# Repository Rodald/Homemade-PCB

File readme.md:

# Homemade-PCB
The goal for this Project is to manufacture PCBs at home using DIY UV photolithography.
This Repository includes two different PCB designs.

## Benchmarking PCB
The benchmark PCB includes 5 different tests:
* Trace width
* Isolation Clearance
* Light Exposure Time & Bleeding
* Drill Hole tests
* Fonts

## Motion Suit PCB
The goal:

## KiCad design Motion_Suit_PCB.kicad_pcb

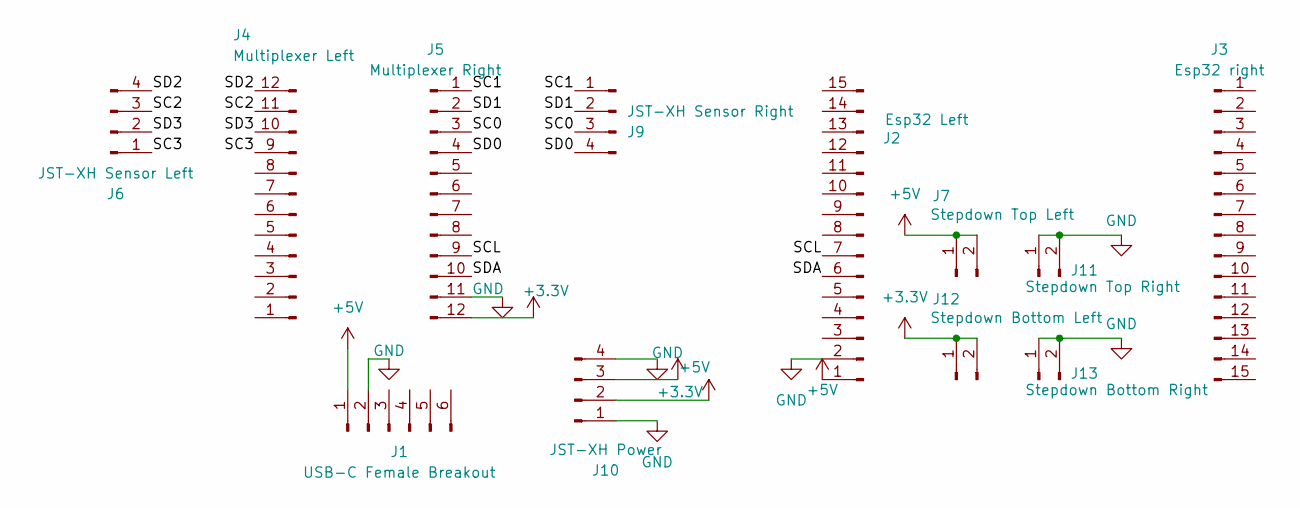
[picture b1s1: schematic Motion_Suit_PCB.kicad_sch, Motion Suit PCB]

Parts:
J1: USB-C Female Breakout; PinHeader_1x06_P2.54mm_Horizontal
J2: Esp32 Left; PinHeader_1x15_P2.54mm_Vertical
J3: Esp32 right; PinHeader_1x15_P2.54mm_Vertical
J4: Multiplexer Left; PinHeader_1x12_P2.54mm_Vertical
J5: Multiplexer Right; PinHeader_1x12_P2.54mm_Vertical
J6: JST-XH Sensor Left; JST_XH_B4B-XH-A_1x04_P2.50mm_Vertical
J7: Stepdown Top Left; PinHeader_1x02_P2.54mm_Horizontal
J9: JST-XH Sensor Right; JST_XH_B4B-XH-A_1x04_P2.50mm_Vertical
J10: JST-XH Power; JST_XH_B4B-XH-A_1x04_P2.50mm_Vertical
J11: Stepdown Top Right; PinHeader_1x02_P2.54mm_Horizontal
J12: Stepdown Bottom Left; PinHeader_1x02_P2.54mm_Horizontal
J13: Stepdown Bottom Right; PinHeader_1x02_P2.54mm_Horizontal

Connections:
+3.3V: J5.12, J10.2, J12.1, J12.2
+5V: J1.1, J2.1, J7.1, J7.2, J10.3
/SC0: J5.3, J9.3
/SC1: J5.1, J9.1
/SC2: J4.11, J6.3
/SC3: J4.9, J6.1
/SCL: J2.7, J5.9
/SD0: J5.4, J9.4
/SD1: J5.2, J9.2
/SD2: J4.12, J6.4
/SD3: J4.10, J6.2
/SDA: J2.6, J5.10
GND: J1.2, J2.2, J5.11, J10.1, J10.4, J11.1, J11.2, J13.1, J13.2

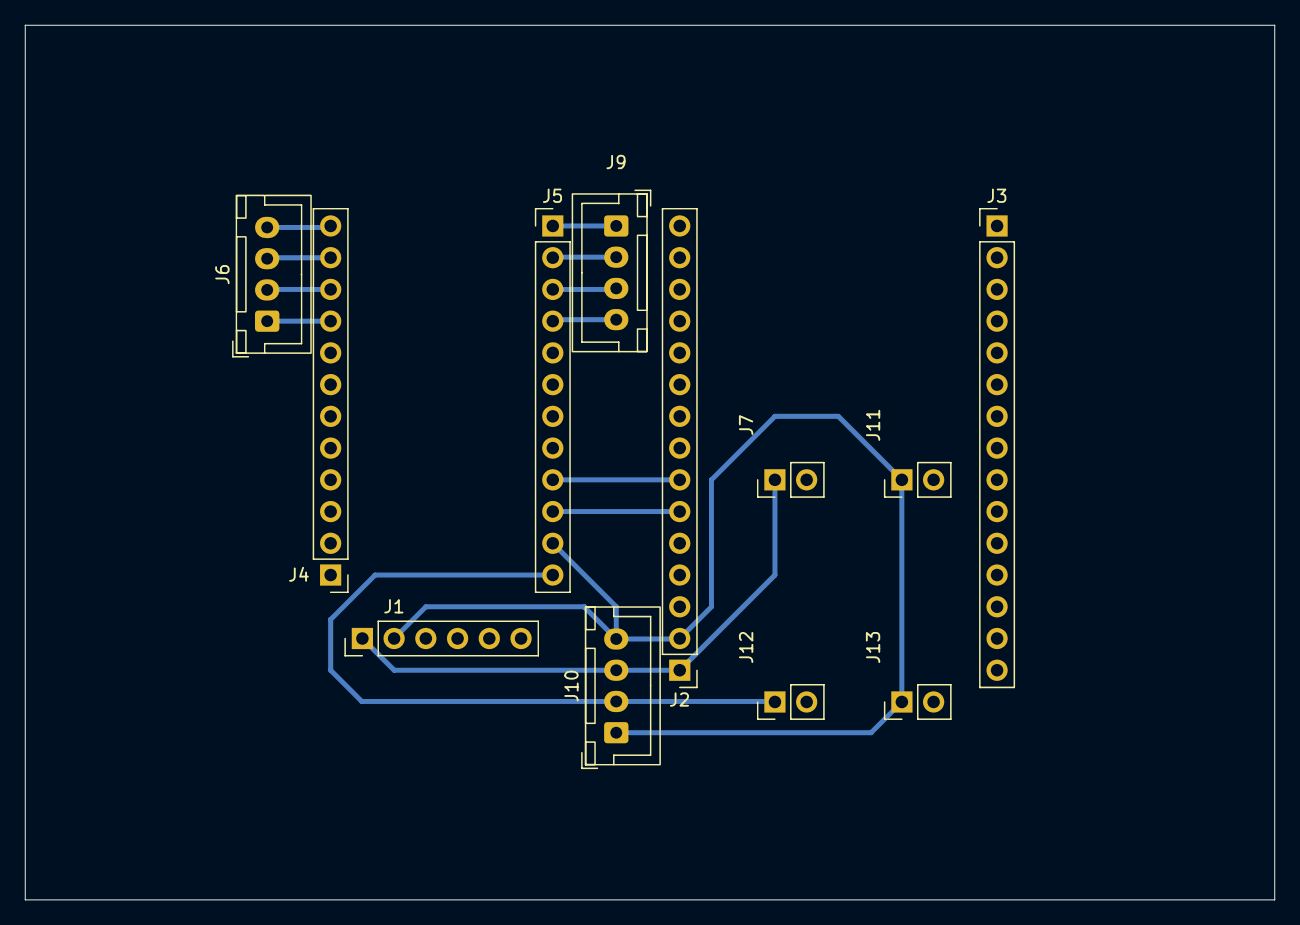
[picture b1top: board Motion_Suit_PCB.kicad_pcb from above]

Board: 2 copper layers, 100.0 x 70.0 mm, 12 parts (0 on the bottom side), 13 nets.

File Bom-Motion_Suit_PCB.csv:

"Reference","Qty","Value","DNP","Exclude from BOM","Exclude from Board","Exclude from Simulation","Exclude from Position Files","Footprint","Datasheet"
"J1","1","USB-C Female Breakout","","","","","${EXCLUDE_FROM_POS_FILES}","Connector_PinHeader_2.54mm:PinHeader_1x06_P2.54mm_Horizontal",""
"J2","1","Esp32 Left","","","","","${EXCLUDE_FROM_POS_FILES}","Connector_PinHeader_2.54mm:PinHeader_1x15_P2.54mm_Vertical",""
"J3","1","Esp32 right","","","","","${EXCLUDE_FROM_POS_FILES}","Connector_PinHeader_2.54mm:PinHeader_1x15_P2.54mm_Vertical",""
"J4","1","Multiplexer Left","","","","","${EXCLUDE_FROM_POS_FILES}","Connector_PinHeader_2.54mm:PinHeader_1x12_P2.54mm_Vertical",""
"J5","1","Multiplexer Right","","","","","${EXCLUDE_FROM_POS_FILES}","Connector_PinHeader_2.54mm:PinHeader_1x12_P2.54mm_Vertical",""
"J6","1","JST-XH Sensor Left","","","","","${EXCLUDE_FROM_POS_FILES}","Connector_JST:JST_XH_B4B-XH-A_1x04_P2.50mm_Vertical",""
"J7","1","Stepdown Top Left","","","","","${EXCLUDE_FROM_POS_FILES}","Connector_PinHeader_2.54mm:PinHeader_1x02_P2.54mm_Horizontal",""
"J9","1","JST-XH Sensor Right","","","","","${EXCLUDE_FROM_POS_FILES}","Connector_JST:JST_XH_B4B-XH-A_1x04_P2.50mm_Vertical",""
"J10","1","JST-XH Power","","","","","${EXCLUDE_FROM_POS_FILES}","Connector_JST:JST_XH_B4B-XH-A_1x04_P2.50mm_Vertical",""
"J11","1","Stepdown Top Right","","","","","${EXCLUDE_FROM_POS_FILES}","Connector_PinHeader_2.54mm:PinHeader_1x02_P2.54mm_Horizontal",""
"J12","1","Stepdown Bottom Left","","","","","${EXCLUDE_FROM_POS_FILES}","Connector_PinHeader_2.54mm:PinHeader_1x02_P2.54mm_Horizontal",""
"J13","1","Stepdown Bottom Right","","","","","${EXCLUDE_FROM_POS_FILES}","Connector_PinHeader_2.54mm:PinHeader_1x02_P2.54mm_Horizontal",""
